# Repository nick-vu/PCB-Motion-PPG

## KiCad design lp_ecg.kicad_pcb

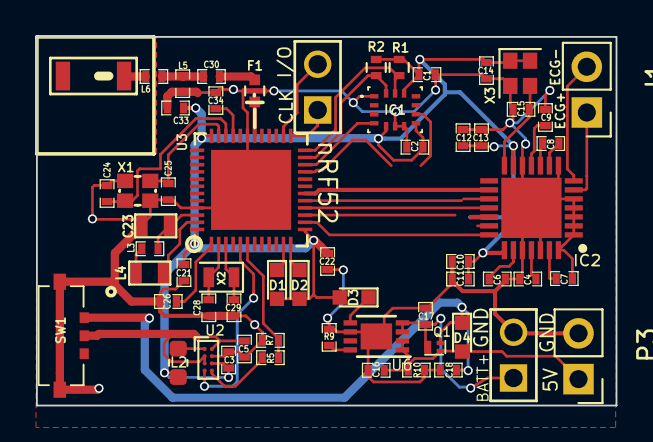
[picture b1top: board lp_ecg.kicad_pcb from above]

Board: 2 copper layers, 32.2 x 20.5 mm, 60 parts (0 on the bottom side), 48 nets.

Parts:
A1: CHIP-ANT; JTI-2450AT18A100-CHIP-ANT
C1, C2, C22, C26, C33: 100nF; SM0402
C3, C4, C5, C6, C11, C13: 10uF; SM0402
C7, C8, C9: 1uF; SM0402
C10, C12, C14: 0.1uF; SM0402
C15: 15pF; SM0402
C16, C17: 4.7uF; SM0402
C18: 1.0uF; SM0402
C21: 4.7µF; SM0402
C23: 1.0µF; SM0603
C24, C25, C28, C29: 12pF; SM0402
C30: 1.0pF; SM0402
C34: 100pF; SM0402
D1, D2, D3: LED; LED_0603
D4: D_Schottky; LED_0603
F1: 2450FM07A0029; R_0402
IC1: BMI160
IC2: MAX30003CTI+; QFN50P500X500X80-29N
J1: Conn_01x02_Male; Pin_Header_Straight_1x02_Pitch2.54mm
L2: 2.20µH; L_0603_1608Metric
L3: 15nH; SM0402
L4: 10uH; SM0603
L5: 2.7nH; SM0402
L6: 3.9nH; SM0402
P1, P2: CONN_2; PIN_ARRAY_2X1
P3: CONN_2; Pin_Header_Straight_1x02_Pitch2.54mm
Q1: DMP21D5UFB4-7B; X2-DFN1006
R1, R2: 30k; R_0402
R5, R7: 1M; SM0402
R9: 2k; SM0402
R10: 100k; SM0402
SW1: SSAJ120100
U2: TPS62746; Texas_DSBGA-8_0.9x1.9mm_Layout2x4_P0.5mm
U3: NRF528XX-QFAA; UQFN-48-1EP_6x6mm_Pitch0.4mm
U6: MCP73831; DFN-8-1EP_3x2mm_Pitch0.5mm
X1: Crystal_GND24; CRYSTAL-SMD-2.0MMx1.6MM
X2: 32.768 kHz; Crystal_SMD_2012-2pin_2.0x1.2mm
X3: KX2013E0032.768000; Crystal_SMD_2016-4pin_2.0x1.6mm

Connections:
1.8V: C1.1, C2.1, C3.1, C10.2, C11.1, C12.1, C13.2, C14.1, C21.2, C22.1, C33.2, D1.2, D2.2, D3.2, IC1.5, IC1.8, IC1.12, IC2.13, IC2.19, IC2.22, L2.2, R1.1, R2.1, U2.C2, U3.13, U3.36, U3.48, X3.1, X3.4
5V_in_charge: C16.1, D4.2, P3.1, Q1.1, R10.1, U6.1, U6.2
/AIN_BAT_DIV_VOLTAGE: R5.2, R7.2, U3.6
/BATT_IN: C17.1, P1.1, Q1.2, U6.3, U6.4
/BMI_INT1: IC1.4, U3.22
/BMI_INT2: IC1.9, U3.21
/BMI_SCL: IC1.13, R1.2, U3.24
/BMI_SDA: IC1.14, R2.2, U3.23
/DEC1: C26.1, U3.1
/DEC3: C34.1, U3.33
/LED2: D1.1, U3.11
/LED3: D2.1, U3.12
/LOAD_SW_CTRL: U2.D1, U3.5
/MAX30003_CSB: IC2.15, U3.19
/MAX30003_FCLK: C15.1, IC2.14, X3.3
/MAX30003_INT: IC2.21, U3.14
/MAX30003_INT2: IC2.20, U3.15
/MAX30003_SCLK: IC2.16, U3.18
/MAX30003_SDI: IC2.17, U3.17
/MAX30003_SDO: IC2.18, U3.16
/RF: C30.1, F1.4
/SWDCLK: P2.1, U3.25
/SWDIO: P2.2, U3.26
DGND: C1.2, C2.2, C3.2, C4.1, C5.2, C6.2, C7.2, C9.2, C10.1, C11.2, C12.2, C13.1, C14.2, C15.2, C16.2, C17.2, C18.1, C21.1, C22.2, C23.2, C24.1, C25.1, C26.2, C28.2, C29.2, C33.1, C34.2, F1.1, F1.3, IC1.1, IC1.6, IC1.7, IC2.1, IC2.2, IC2.3, IC2.4, IC2.5, IC2.8, IC2.12, IC2.24, IC2.26, IC2.28, IC2.29, L5.2, P1.2, P3.2, R7.1, R9.2, R10.2, SW1.4, SW1.5, U2.B2, U3.31, U3.45, U3.49, U6.6, U6.9, X1.2, X1.4, X3.2
unnamed: A1.1, L6.2
unnamed: C4.2, IC2.25
unnamed: C6.1, IC2.23
unnamed: C7.1, IC2.27
unnamed: C8.1, IC2.10
unnamed: C8.2, IC2.9
unnamed: C9.1, IC2.11
unnamed: C23.1, L3.2, U3.46
unnamed: C24.2, U3.34, X1.1
unnamed: C25.2, U3.35, X1.3
unnamed: C28.1, U3.2, X2.2
unnamed: C29.1, U3.3, X2.1
unnamed: C30.2, L5.1, L6.1
unnamed: D3.1, U6.5
unnamed: F1.2, U3.30
unnamed: IC2.6, J1.1
unnamed: IC2.7, J1.2
unnamed: L2.1, U2.A1
unnamed: L3.1, L4.2
unnamed: L4.1, U3.47
unnamed: R5.1, U2.D2
unnamed: R9.1, U6.8
VCC: C5.1, SW1.3, U2.A2, U2.B1, U2.C1
VccSwitch: C18.2, D4.1, Q1.3, SW1.1

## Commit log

2019-04-03 Initial commit. Duplicated from PCB_nRF52_ADS1292_recharge.
2019-04-04 Added new libs, removed load switch, added TPS62746
2019-04-04 Removed all components associated with ADS1292.
2019-04-04 Fully updated ICM in PCB.
2019-04-04 Fixed netlist for ICM (3V3→1V8)
2019-04-04 Fully realized schematic and pcb awaiting final check.
2019-04-04 Changed footprint for MCP6001 from SC-70-5 to SOT-23-5.
2019-04-04 Updated gerber files.
2020-06-24 Adding Altium Importer
